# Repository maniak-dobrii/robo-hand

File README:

Robo hand work in progress, hand itself is based on [design by Juan Gutierrez](https://www.thingiverse.com/thing:14986). In original design I didn't like thumb placement.

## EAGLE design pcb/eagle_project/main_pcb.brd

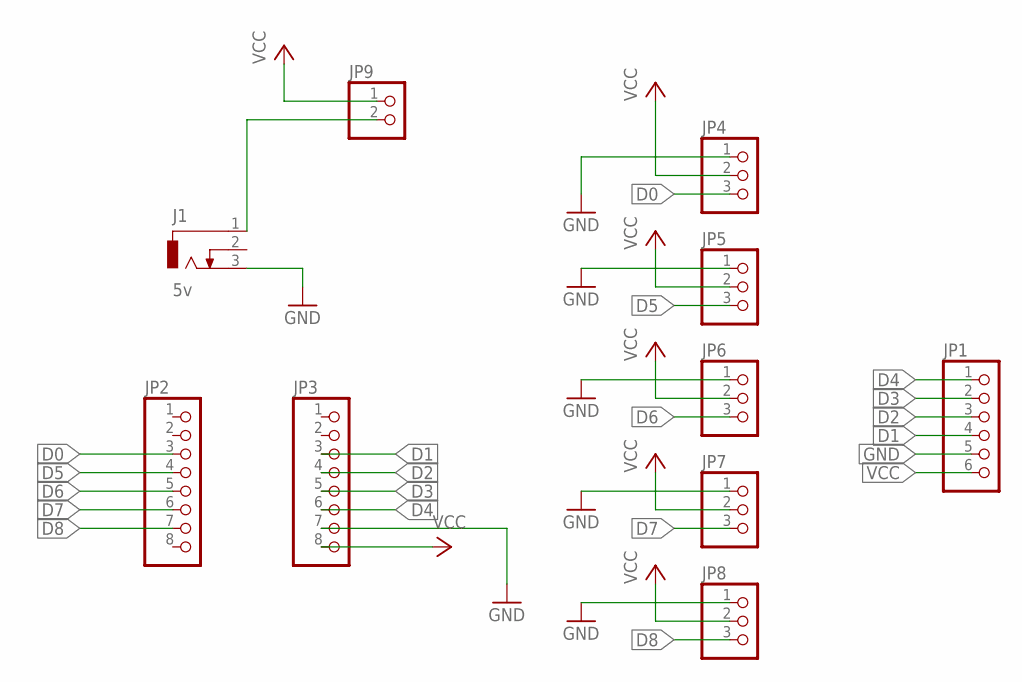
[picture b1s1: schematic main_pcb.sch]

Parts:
J1: 5v; DCJ0303
JP1: PINHD-1X6; 1X06
JP2, JP3: PINHD-1X8; 1X08
JP4, JP5, JP6, JP7, JP8: PINHD-1X3; 1X03
JP9: PINHD-1X2; 1X02

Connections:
D0: JP2.3, JP4.3
D1: JP1.4, JP3.3
D2: JP1.3, JP3.4
D3: JP1.2, JP3.5
D4: JP1.1, JP3.6
D5: JP2.4, JP5.3
D6: JP2.5, JP6.3
D7: JP2.6, JP7.3
D8: JP2.7, JP8.3
GND: J1.3, JP1.5, JP3.7, JP4.1, JP5.1, JP6.1, JP7.1, JP8.1
unnamed: J1.1, JP9.2
VCC: JP1.6, JP3.8, JP4.2, JP5.2, JP6.2, JP7.2, JP8.2, JP9.1

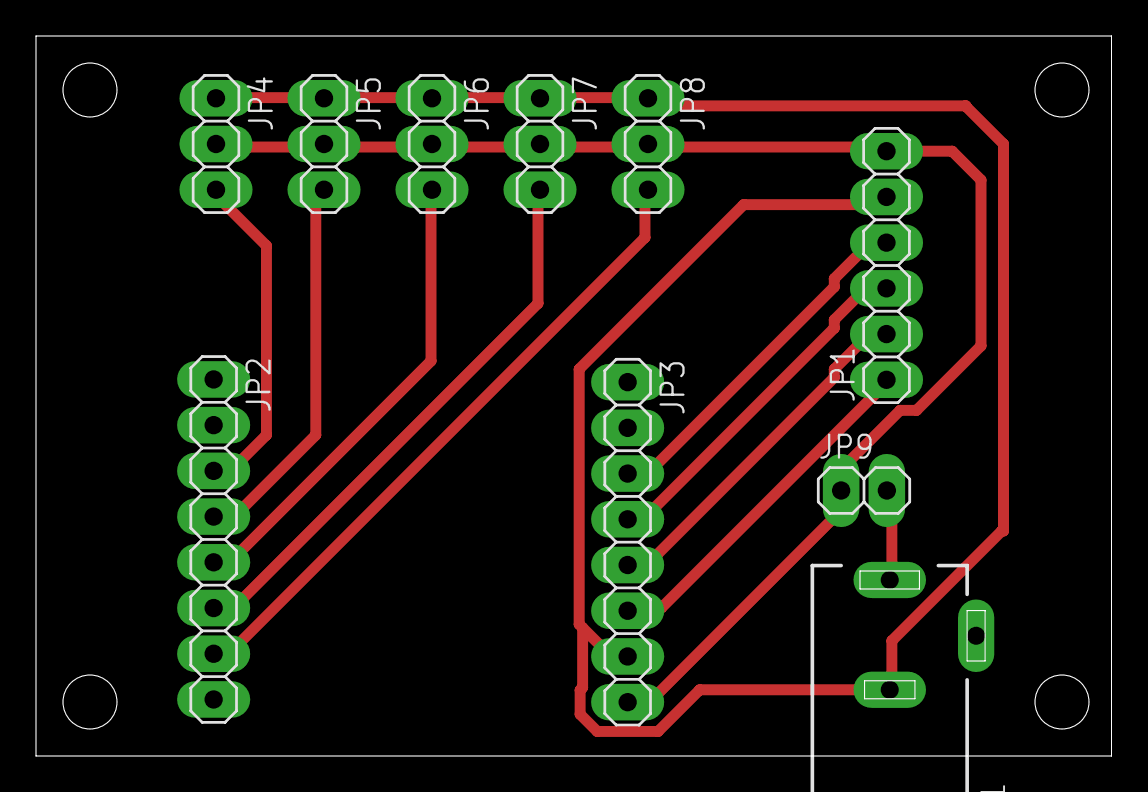
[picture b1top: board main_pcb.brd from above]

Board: 1 copper layer, 59.8 x 40.0 mm, 10 parts (0 on the bottom side), 12 nets.

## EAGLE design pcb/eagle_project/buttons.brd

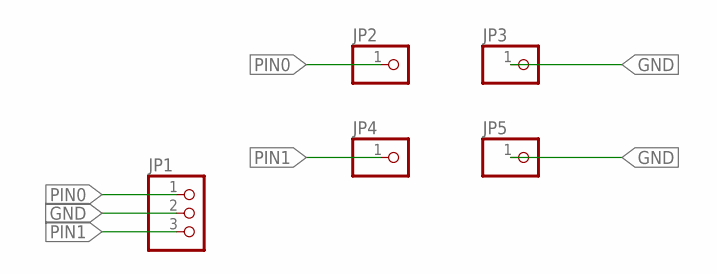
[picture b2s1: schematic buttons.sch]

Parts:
JP1: PINHD-1X3; 1X03
JP2, JP3, JP4, JP5: PINHD-1X1; 1X01

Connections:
GND: JP1.2, JP3.1, JP5.1
PIN0: JP1.1, JP2.1
PIN1: JP1.3, JP4.1

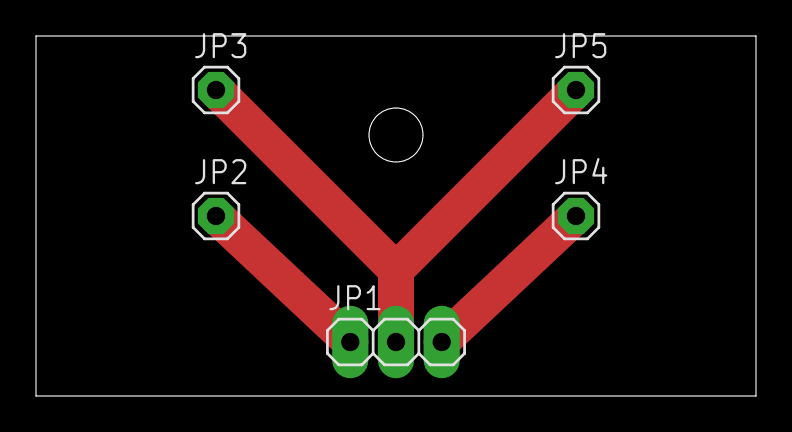
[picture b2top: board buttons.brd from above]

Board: 1 copper layer, 40.0 x 20.0 mm, 5 parts (0 on the bottom side), 3 nets.

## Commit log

2017-09-17 Initial messy loadup
2017-09-17 Removed all generatable files except finger gcode
2017-09-17 Added dummy readme to mention original hand design this work is based on
2017-09-17 Rename README to README.md
2017-09-17 Moved gcode to dedicated directory
2017-09-17 Cleaned main skp file
2017-09-17 Added SG90 servo with field + readme mentions
2017-09-17 Servos with new bindings first arrangement
2017-09-17 Added new driver idea (raw incorrect size)
2017-09-20 Added driver profile
2017-09-20 Added driver ring
2017-09-20 Added bindings (not yet added to the driver ring)
2017-09-20 Joined bindings to the driver ring
2017-09-21 Added first driver version stl, gcode
2017-09-21 Added 45mm driver ring
2017-09-21 Added 45mm driver
2017-09-21 Rotaded servos taking into account wires position
2017-10-30 Updated driver relative x/y positions
2017-10-30 Refined servo sizes
2017-10-30 First servo holders (without additional 'corners' for better stability)
2017-10-31 Unmerged first try driver holder
2017-10-31 Jined servo holder, with tight holes
2017-11-05 Increased servo holder hole diameter to 1.6mm
2017-11-05 Removed bazilion redundunt guides
2017-11-05 Added servo holders to servo components
2017-11-05 Arranged servos and angle changers
2017-11-06 Updated box sizes, added honeycomb grid surface
2017-11-06 Updated box dimensions, added honeycomb pattern as separate file
2017-11-12 Sized case base
2017-11-12 Sized case base to 164x134mm
2017-11-12 Formed case bottom plate without holes and joined servo holders
2017-11-12 Added case bottom plate copy to the scene
2017-11-12 Decided to keep walls 6mm(3mm separator, 3mm bolt hole), extruded front panel without holes and top notches
2017-11-12 Added front to bottom panel mounting holes
2017-11-12 Added bevel to bottom plate
2017-11-19 Extended base length to 170mm, added temporary back panel, positioned pcb
2017-11-19 Added pcb stands
2017-11-25 Merged full bottom base
2017-11-25 Separating bottom plate: added first cut (holes not cut)
2017-11-25 Fixed bottom plate holes
2017-11-25 Added one more cut to the bottom plate
2017-11-25 Separated bottom plate into two parts (without holes)
2017-11-25 Updated strings holder, added handles
2017-11-25 Added strings holder hole mounts to the front panel
2017-11-25 Added side panel frames (without holes)
2017-11-25 Removed internal wall from the back panel, frame first, details later
2017-11-25 Created intercomponent holes in the bottom panel
2017-11-26 Added side holes to the front and side panels
2017-11-26 Added holes for bottom plate fishing line joints
2017-12-03 Not sure what, but used to print second part of the bottom panel
2017-12-17 New top buttons module, redesigned back, top and right panel (including holes, honeycomb pattern and switch socket)
2017-12-17 Redesigned top panel (turned honeycomb 45%)
2017-12-17 Adjusted top panel front part to repeat palm shape better
2017-12-17 Small tweaks here and there
2017-12-24 Fixed buttons model (left button got clamped during gcode generation)
2017-12-24 Added simplified hands with gestures for button icons
2017-12-24 Button pictures before subtraction
2017-12-24 (fixed bottoms) Button pictures before subtraction
2017-12-26 Updated string positioner by adding security caps to avoid string jumping off
2018-01-02 Added separate palm .skp
2018-01-08 Removed all redundant stuff, added missing binding holes (front panel to top panel) that I forgot to add previously
2018-01-08 Fixed palm absolute position
2018-01-08 Moved nut hole to separate file
2018-01-08 Moved button icons to separate file
2018-01-08 Removed redundant files
2018-01-08 Moved 3D models to separate directory
2018-01-08 Added pretty shamefull pcb design, hope nobody sees it, wait, I'm putting it on the internet, ook
2018-01-08 Added prototype firmware (buttons only, no wifi)
2018-01-13 Added gif for readme
2018-01-13 Added note on firmware
2018-05-20 Dirty command loop implementation, my C++-foo needs refreshment=) Firmware is bloated with redundant/dirty code.
2018-05-20 Refactored PalmHardware into separamte class
2018-05-20 Refactored button listening routine into separate class, PalmHardware now listens to button events via ButtonListener and translates them to the outer world. New button-control UX, fast press to show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
2018-05-20 Hooked over-Wi-Fi control along with hardware buttons control
2018-05-20 Updated README to reflect recent basic Wi-Fi control additions
2018-05-27 Added demo gif for the first pre-release
2018-06-17 Added robo-hand ios app skeleton with some data layer stuff. Some experimental and simplifyed stuff here.
2018-06-17 Fixed missing @escaping, updated gitignore
2018-06-17 Fixed missing .gitignore specifications for Xcode-generated files
2018-06-17 Added test robo-hand ios app version, that uses 0.0.1 robo-hand JSON API with hardcoded http://192.168.4.1/ base url
2018-08-05 Updated project to Swift 4.2
2018-08-12 Refactored palm control routines into service
2018-08-20 Refactored app to use modules and such stuff, lost my battle to perfectionism a bit, but got back on track and crutched stuff up along with questionable experiments \m/
